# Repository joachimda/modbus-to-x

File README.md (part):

# Modbus-to-X

An ESP32-based hardware and firmware stack that bridges RS-485/Modbus field devices to modern network services such as MQTT, with a configuration-first UX for installers and maintainers.

## Table of Contents
- [Overview](#overview)
- [Architecture](#architecture)
  - [Hardware](#hardware)
  - [Firmware](#firmware)
- [Getting Started](#getting-started)
  - [Prerequisites](#prerequisites)
  - [Build and Flash](#build-and-flash)
  - [Release Automation](#release-automation)
  - [Local UI Development](#local-ui-development)
  - [HTTP API](#http-api)
- [Usage](#usage)
  - [First Boot and Network Setup](#first-boot-and-network-setup)
  - [Configuring Modbus Devices](#configuring-modbus-devices)
  - [MQTT Publishing](#mqtt-publishing)
  - [OTA Updates](#ota-updates)
- [Project Structure](#project-structure)
  - [Hardware Documentation](#hardware-documentation)
  - [Software Documentation](#software-documentation)
- [Acknowledgements](#acknowledgements)

## Overview
Modbus-to-X combines a custom ESP32 carrier board with firmware that polls Modbus RTU devices over RS-485, persists telemetry locally, and republishes structured payloads to MQTT brokers. 
The firmware exposes an onboard web interface for Wi-Fi provisioning, Modbus configuration, live device statistics, and log retrieval so field technicians can deploy the gateway without recompiling binaries.

## Architecture
The project is split between dedicated hardware design files and a PlatformIO firmware project. Hardware-specific documentation lives in [`hardware/`](hardware/); firmware, tooling, and UI assets live in [`software/`](software/).

### Hardware
- Four-layer ESP32 carrier featuring an ESP32-WROOM-32D module, MAX3485 RS-485 transceiver
- RJ12 Connector exposing differential RS-485 pair alongside field power for quick deployment.
- Wide input voltage range (4.5 - 30V)
- Supporting assets include datasheets, the hardware release policy, the compatibility table and a release record for each board revision under `hardware/`.

### Firmware
- PlatformIO-based ESP32 application primarily built with the Arduino framework.
- Library dependencies: ModbusMaster, PubSubClient, ArduinoJson, and ESPAsyncWebServer for protocol handling and a dynamic UI backend.
- A custom partition table separates user configurations from UI components, leaving user configurations untouched on filesystem uploads.
- Boot sequence mounts filesystem partitions, starts the async web server ("MBX Server"), initializes the Modbus scheduler, and spins up the MQTT manager.
- Configuration data for the Modbus bus, devices, and MQTT settings is stored in `/conf/*.json` on the dedicated config SPIFFS partition (`cfg`) and hot-reloaded without reflashing.
- MQTT passwords are stored in NVS preferences; `/conf/mqtt.json` contains non-sensitive fields.
- Default wiring, RS-485 guard times, Wi-Fi AP Portal credentials, and OTA parameters are centralized in [`Config.h`](software/modbus-to-mqtt/include/Config.h).
- Signed and manual HTTP updates use a bounded quiescence coordinator and a compiled recovery page; the lifecycle and protocol are documented in [`OTA_LIFECYCLE.md`](OTA_LIFECYCLE.md).

## Getting Started

### Prerequisites
- Modbus-to-X hardware (v0.2 alpha or later) and Modbus RTU devices wired to the RS-485 terminals.
- 4.5–40 VDC field power (buck input validated in the current design) and a USB-to-UART adapter if not using OTA uploads.
- Development host with Python 3, [PlatformIO Core](https://platformio.org/install/cli), and a working `git` toolchain. Required Python build dependencies are installed automatically by `scripts/install_build_deps.py` when PlatformIO runs.

### Build and Flash
1. Clone the repository and enter the firmware workspace:
   ```bash
   git clone https://github.com/joachimda/modbus-to-x.git
   cd modbus-to-x/software/modbus-to-mqtt
   ```
2. Choose an environment in `platformio.ini`:
   - `mbx-custom-board-dev` — development build, serial upload (default).
   - `mbx-custom-board-dev-ota` — development build, OTA upload (reads the device address from `MBX_DEV_OTA_HOST` and the OTA password from `MBX_DEV_OTA_PASSWORD`).
   - `mbx-custom-board-release` — release build (used by the GitHub Actions workflow).
   - `mbx-custom-board-release-primer` — primes a dev device to receive HTTP OTA updates (same environment variables as `mbx-custom-board-dev-ota`).
3. Build the firmware (PlatformIO will fetch dependencies and embed git metadata):
   ```bash
   pio run
   ```
4. Flash via USB/UART or OTA by selecting the matching environment:
   ```bash
   # Serial upload
   pio run -e mbx-custom-board-dev -t upload

   # OTA upload to a provisioned gateway; address and password come from your shell
   export MBX_DEV_OTA_HOST=<device-ip> MBX_DEV_OTA_PASSWORD=<ota-password>
   pio run -e mbx-custom-board-dev-ota -t upload
   ```
5. Upload the web UI and config assets to SPIFFS when they change:
   ```bash
   pio run -e mbx-custom-board-dev -t uploadfs
   ```

### Release Automation
Pushing a `v*` tag triggers the GitHub Actions workflow in `.github/workflows/main.yml` to build firmware + filesystem images and create a GitHub Release with the assets:
- `modbus-to-x.bin` (firmware)
- `modbus-to-x.fs.bin` (filesystem)
- `modbus-to-x.notes.txt` (release notes generated from the commit log since the previous tag)
- `modbus-to-x.manifest.json` (includes SHA-256 hashes and a signature generated from `OTA_SIGNING_KEY_PEM` and `KID`).

The same workflow can also be started manually (Actions → "Release OTA" → "Run workflow", or `gh workflow run "Release OTA" --ref main -f version=8.0.5-beta`). Enter the bare version without the `v` (`8.0.5` or `8.0.5-beta.1`); the workflow creates the tag `v<version>` on the selected ref (`gh` uses the repository's default branch when `--ref` is omitted), builds exactly as a tag push would, and pushes the tag together with the release. It refuses to run if that tag already exists or if the selected commit already carries a tag.

### Local UI Development
The `scripts/run_test_webserver.py` helper serves the `data/` directory with mocked API responses so you can iterate on the HTML/JS bundle without flashing the device:
```bash
cd software/modbus-to-mqtt
python3 scripts/run_test_webserver.py
# Visit http://127.0.0.1:8000
```
It injects correct MIME types, disables caching, and emulates the SPA's system, OTA, and administrative API behavior, including mutation-request protection.

Use `--provisioning-scenario delayed`, `temporary`, `completion-unavailable`, `readiness-html`, or another listed scenario to exercise captive handoff failures. Running the mock on port 80 allows its loopback station address to complete the full dashboard handoff.

Use `--ota-scenario success`, `failure`, or `sse-loss` to exercise OTA
admission, lifecycle progress, status-poll fallback, recovery, and reboot UI.

### HTTP API

See the [HTTP API request contract](HTTP_API.md) for the route and method matrix, browser cross-site protections, OTA authorization behavior, and non-browser client examples.

## Usage

### First Boot and Network Setup
1. Power the gateway; it will advertise a Wi-Fi AP using the defaults defined in `Config.h` (`MODBUS-MQTT-BRIDGE` / `you-shall-not-pass`).
2. Connect to the AP. The ESP will try getting 192.168.4.1 from DHCP. If supported on your OS, you will be prompted to open the Captive Portal and redirected automatically. If these fail, check your router for the device's IP address, and use your browser to open the configuration page `http://192.168.4.1/`. 
3. Follow the on-screen guidance to scan, join, or provision hidden networks, optionally specifying static IP parameters before saving.
4. After a saved network connection succeeds, the portal requests an acknowledged reboot, waits for the device to return in station mode, and opens the dashboard at the reported address. Temporary connections remain in the portal until a saved attempt succeeds.

### Configuring Modbus Devices
- Use **Configure Modbus** to edit the RS-485 bus, add devices, and define datapoints. Modbus configurations are stored in the config partition at `/conf/config.json` and can be applied live without rebooting.
- Configuration files follow the schema in `software/modbus-to-mqtt/data/conf/schema.json`; the excerpt below shows the datapoint fields. Each datapoint specifies the function code, register address, data type, scale, and engineering units that will be published when polled. Registers are decoded by `dataType` before the scale is applied: `int16`/`uint16` use one register (optionally a byte via `registerSlice`), `int32`/`uint32`/`float32` use two and `int64`/`uint64` four registers, in the `wordOrder` `big` (default, first register = most significant word) or `little`. `numOfRegisters` below the type's width is raised to it when the configuration loads. FC6 writes one register, so saving FC6 with a 32-bit or 64-bit type is rejected; a stored configuration that already combines them loads as `uint16` (the encoding every FC6 value had before data types were honoured, so nothing changes for it) with a logged warning.
- `bus.baud` must be an integer of at least 1200, the lowest rate the bus form offers; a configuration below it, or with a non-integer value, is rejected with `invalid_baud_rate`. A stored configuration that fails this check is logged at boot and leaves Modbus disabled until it is corrected in **Configure Modbus**.
- A datapoint's `poll_interval` (seconds) must be a whole number from 0 to 2147483, and `poll_interval_ms` from 0 to 2147483647 (about 24.8 days); `poll_interval_ms` wins when both are present. A save with anything else is rejected with `invalid_poll_interval`. A configuration already stored on the device keeps loading: at boot an out-of-range interval is brought into range (negative becomes 0, a fraction is rounded down, a larger number becomes the maximum) and logged as `poll_interval_repaired`. Enabling Modbus again at runtime polls every datapoint once and restarts its interval. The limit keeps polling deadlines unambiguous when the 32-bit millisecond uptime counter wraps after about 49.7 days.
- Per-device MQTT publishing and Home Assistant discovery can be toggled in the Modbus config; discovery publishes retained entity definitions for read/write datapoints.
  Example (excerpt):
  ```json
  {
    "devices": [
      {
        "name": "Boiler",
        "slaveId": 10,
        "mqttEnabled": true,
        "homeassistantDiscoveryEnabled": true,
        "dataPoints": [
          {
            "id": "temp",
            "name": "Temperature",
            "function": 4,
            "address": 100,
            "numOfRegisters": 1,
            "dataType": "int16",
            "scale": 0.1,
            "unit": "C",
            "topic": "plant/boiler/temp_c"
          },
          {
            "id": "flow",
            "name": "Flow",
            "function": 3,
            "address": 200,
            "numOfRegisters": 2,
            "dataType": "float32",
            "wordOrder": "little",
            "scale": 1,
            "unit": "m3/h"
          }
        ]
      }
    ]
  }
  ```

#### Wavin AHC 9000
The Wavin AHC 9000 floor-heating controller (also sold as Jablotron AC-116) uses Modbus RTU framing but answers only its own function codes, so standard reads return `IllegalFunction`. Use function `67` (0x43, read) and `68` (0x44, write). These address a register by `category`, `page` and a register index, which goes in `address`, each 0-255. Reads cover up to 22 registers; writes set one 16-bit register and follow the FC6 rules.

- Bus: 38400 baud, `8N1`. The controller always answers slave address 1.
- Commonly used registers, from Wavin's Modbus description for the AHC 9000 (14-08-2013, [copy in jascdk/wavin_ahc9000_advanced_mqtt](https://github.com/jascdk/wavin_ahc9000_advanced_mqtt/tree/main/Modbus%20Documentation)) and the community projects ([niklascp/Wavin-AHC-9000-mqtt](https://github.com/niklascp/Wavin-AHC-9000-mqtt), [spiff42/wavin-python](https://github.com/spiff42/wavin-python)), checked on an AHC 9000 with wireless thermostats. Thermostats (elements) and channels are numbered from 0; a channel's page is its output number minus one.

  | Category | Page | Index | Value |
  | --- | --- | --- | --- |
  | 1 (elements) | element/thermostat number | 2 | Channel assignment, bitmask of the channels this thermostat drives |
  | 1 (elements) | element/thermostat number | 4 | Air temperature, `int16` × 0.1 °C |
  | 1 (elements) | element/thermostat number | 8 | Status; bit `0x8000` alive, `0x0800` lost, `0x0200` low battery, `0x0010` is a thermostat |
  | 1 (elements) | element/thermostat number | 9 | RSSI: high byte at the thermostat, low byte at the controller; signed, 0 = -74 dBm, 0.5 dB per step |
  | 1 (elements) | element/thermostat number | 10 | Battery in 10 % steps (9 = 90 %); 0 until the thermostat has reported |
  | 1 (elements) | element/thermostat number | 11 | Primary channel (sync group) |
  | 2 (packed data) | channel number | 0 | Manual setpoint, `int16` × 0.1 °C (writable) |
  | 2 (packed data) | channel number | 1, 2 | Comfort and eco setpoints, `int16` × 0.1 °C |
  | 2 (packed data) | channel number | 4 | Standby setpoint, `int16` × 0.1 °C (writable) |
  | 2 (packed data) | channel number | 7 | Configuration; low 3 bits are the mode (0 manual, 1 permanent standby, 2 eco, 3 comfort, 4 party, 5 holiday) and bit `0x0008` enables the week schedule |
  | 2 (packed data) | channel number | 8, 9 | Minimum and maximum setpoint the user can set on the thermostat, `int16` × 0.1 °C. The controller does not clamp 0x44 writes to this range |
  | 2 (packed data) | channel number | 16 | Desired temperature the channel currently heats to, `int16` × 0.1 °C (read only) |
  | 3 (channels) | channel number | 0 | Timer event; bit `0x0010` is set while the output is on, the low 4 bits are the current timer event (1 idle, 7 output on) |
  | 3 (channels) | channel number | 1 | Actuator current in 0.54 mA units |
  | 3 (channels) | channel number | 2 | Primary element **plus one** in the low 6 bits (`0x00C1` = element 0, 0 = no thermostat); `0x0400` means all thermostats lost; `0x0080`/`0x0040` store the party/holiday preference and `0x4000` means the channel syncs its parameters in the next frame |

  ```json
  {
    "version": 1,
    "bus": { "enabled": true, "baud": 38400, "serialFormat": "8N1" },
    "devices": [
      {
        "name": "Wavin",
        "slaveId": 1,
        "mqttEnabled": true,
        "homeassistantDiscoveryEnabled": true,
        "dataPoints": [
          { "id": "zone1_temp", "name": "Zone 1 temperature", "function": 67,
            "category": 1, "page": 0, "address": 4, "numOfRegisters": 1,
            "dataType": "int16", "scale": 0.1, "unit": "C", "poll_interval": 30 },
          { "id": "zone1_setpoint", "name": "Zone 1 setpoint", "function": 67,
            "category": 2, "page": 0, "address": 0, "numOfRegisters": 1,
            "dataType": "int16", "scale": 0.1, "unit": "C", "poll_interval": 30 },
          { "id": "zone1_setpoint_set", "name": "Zone 1 setpoint", "function": 68,
            "category": 2, "page": 0, "address": 0, "numOfRegisters": 1,
            "dataType": "int16", "scale": 0.1 }
        ]
      }
    ]
  }
  ```
- The clock (category 5, page 0: year, month, day, weekday with 0 = Monday, hour, minute, second) must be read or written as one 7-register page; single-register writes are not answered.
- A wall display (DS-9000) may share the bus as a second master. Bytes that cannot be the reply to the outstanding request (another slave or function, more registers than requested, the display's own requests, or a bad CRC) are skipped while waiting. An attempt waits 500 ms for the reply to start (`WAVIN_TURNAROUND_MS`) plus the time the reply takes at the bus's baud rate (about 13 ms for 22 registers at 38400 8N1, 409 ms at 1200). A read or 0x44 write that times out or fails its CRC is retried after a random 100–250 ms pause, up to 3 attempts in total (`WAVIN_READ_ATTEMPTS`, `WAVIN_WRITE_ATTEMPTS`), but a retry only starts if it still fits the 2000 ms budget for the attempts and their pauses (`WAVIN_TRANSACTION_BUDGET_MS`, derived from the OTA quiescence bound): at 38400 all three attempts normally fit, at 9600 a 22-register read usually gets two, at 1200 one. After a final failure, input is discarded until the line has been quiet for 50 ms (`WAVIN_SETTLE_QUIET_MS`), for at most 150 ms (`WAVIN_SETTLE_MAX_MS`) beyond the budget, so a reply that arrives late is not taken for the reply to the next request. A 0x44 write sets absolute values, so repeating it after a lost reply cannot double-apply; if the same register is changed at the wall display in the 0.6–0.8 s (at 38400) between a lost reply and the retry, the retry overwrites that change (last writer wins, as it does without retries when the display edit follows the write). A reply carrying fewer registers than requested is accepted; only the registers received are decoded.

### MQTT Publishing
- Configure broker host, port, credentials, and optional root topic via the **Configure MQTT** page or by editing `/conf/mqtt.json`. The firmware automatically extracts hostnames from URLs and persists the MQTT password in NVS preferences.
- When Modbus reads succeed, datapoint values are published to MQTT using either the exact per-datapoint topic override or the default pattern `<root>/<device>/<datapoint>` with slugified device and datapoint names.
- Published values are decoded by the datapoint's `dataType` (and `wordOrder` for multi-register types) before the scale is applied, then printed with as many decimals as the scale has (`0.01` → `-2.00`, `1` → `1234`, `0.5` → `12.5`); `float32` values print the shortest decimal (7 to 9 significant digits) that reads back as the same value; `int64`/`uint64` values keep every digit at integral scales and round through double precision at fractional ones. Coils and discrete inputs publish `1`/`0`; `TEXT` datapoints publish the ASCII content of their registers. A read that returns fewer registers than the data type needs is logged and not published.
- A writable datapoint treats its configured `topic` as a base and subscribes only to `<base>/set`; an empty base uses the same default resolution as a readable datapoint before `/set` is appended. Commands must be published without MQTT retain. There is deliberately no subscription on the legacy base/state topic.
- Existing state consumers require no changes. Existing command publishers and automations must migrate from `<base>` to `<base>/set`; retained state left on `<base>` is safe because the gateway no longer subscribes there.
- Home Assistant sensors advertise the resolved state topic. Switches and numbers advertise the derived `/set` command topic and use a readable datapoint with the same resolved base as state feedback, or remain optimistic when no matching read exists. Number entities advertise the data type's range times the scale as `min`/`max` and the absolute scale as `step` (never below Home Assistant's minimum of `0.001`).
- FC5 coil commands accept only `0`, `1`, `false`, or `true` after surrounding whitespace is removed; the words are case-insensitive.
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
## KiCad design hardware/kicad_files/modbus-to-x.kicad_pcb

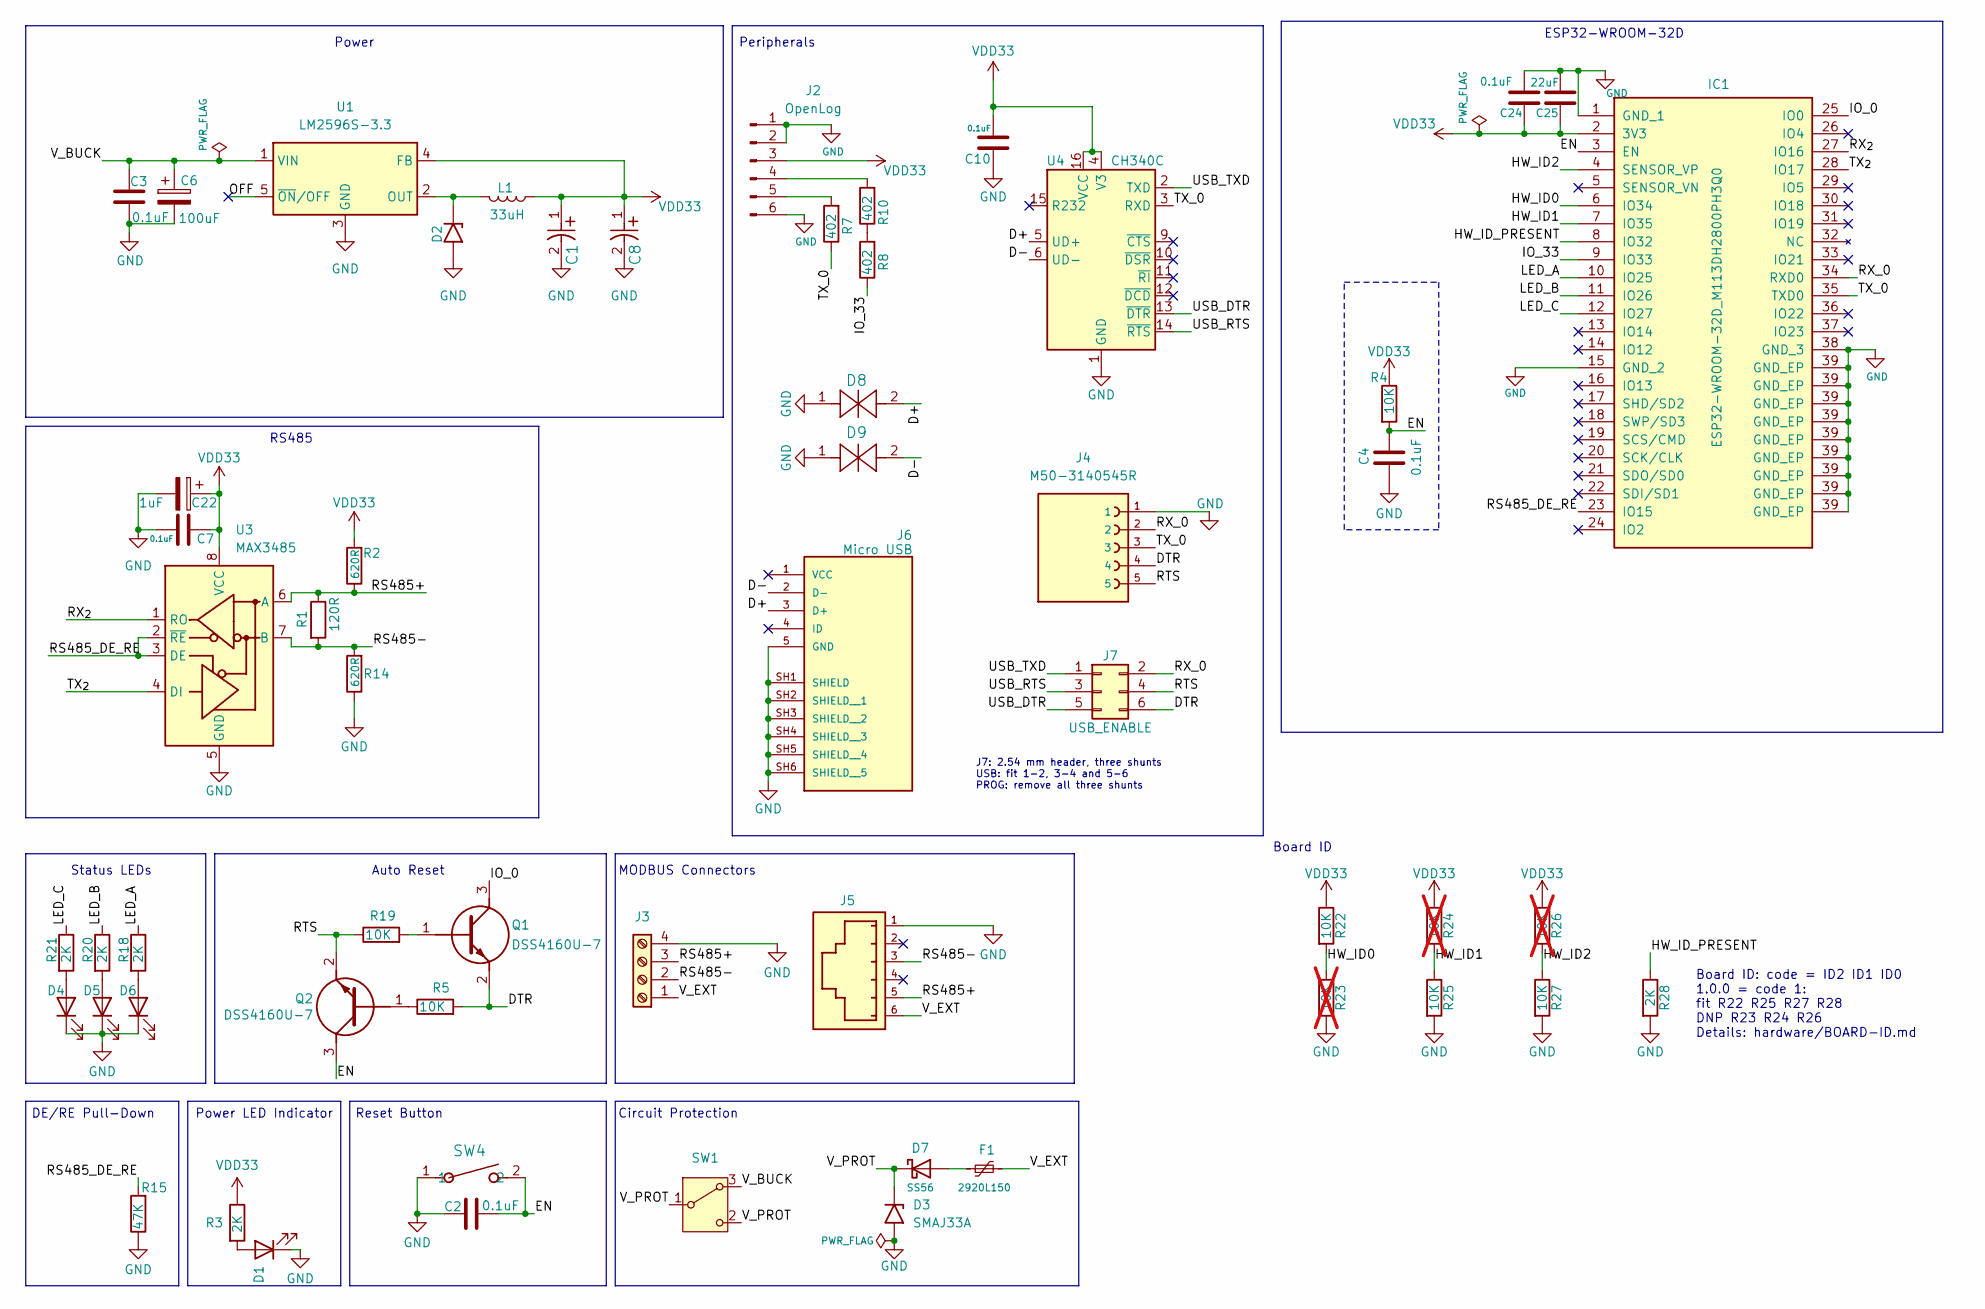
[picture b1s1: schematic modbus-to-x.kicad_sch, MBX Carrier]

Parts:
C1, C8: 330uF; T495D337K006ATE100; MPN T495D337K006ATE100
C2, C4, C7, C10, C24: 0.1uF; C_0805_2012Metric; Voltage 50V; MPN GCD21BR71H104KA01L
C3: 0.1uF; C_0603_1608Metric; Voltage 50V; MPN C0603C104K5RACTU
C6: 100uF; ESY107M050AG3AA; Voltage 50V; MPN ESY107M050AG3AA
C22: 1uF; CP_Elec_4x5.4; Voltage 50V; MPN NACE1R0M50V4X5.5TR15F
C25: 22uF; C_0805_2012Metric_Pad1.18x1.45mm_HandSolder; Voltage 16V; MPN CL21A226MOCLRNC
D1, D4, D5, D6: LED; LED_0402_1005Metric_Pad0.77x0.64mm_HandSolder; MPN LW QH8G-Q2OO-3K5L-1
D2: B340LA-13-F; D_SMA_Handsoldering; MPN B340LA-13-F
D3: SMAJ33A; D_SMA; MPN SMAJ33A
D7: SS56; D_SMA; MPN SS56
D8, D9: PESD0402-140; PESD0402-140_LTF; MPN PESD0402-140
F1: 2920L150; Fuse_2920_7451Metric; MPN 2920L150/60MR
IC1: ESP32-WROOM-32D_M113DH2800PH3Q0; ESP32-WROOM-32D_ANT_SILK_REMOVED; MPN M113DH2800PH3Q0
J2: OpenLog; MBX_PinHeader_1x06_P2.54mm_Vertical; MPN Pin Header 2.54mm (Mixed lengths)
J3: Screw_Terminal_01x04; TerminalBlock_Phoenix_MKDS-1,5-4-5.08_1x04_P5.08mm_Horizont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
J4: M50-3140545R; HARWIN_M50-3140545R; MPN M50-3140545R
J5: 615006138421; RJ12_615006138421; MPN 615006138421
J6: Micro USB; AMPHENOL_10118194-0001LF; MPN 10118194-0001LF
J7: USB_ENABLE; PinHeader_2x03_P2.54mm_Vertical; MPN Pin Header 2.54mm (Mixed lengths)
L1: 33uH; IND_BOURNS_SRR1260; MPN SRR1260-330M
Q1, Q2: DSS4160U-7; SOT65P210X110-3N; MPN DSS4160U-7
R1: 120R; R_1206_3216Metric_Pad1.30x1.75mm_HandSolder; MPN RC1206FR-13120RL
R2, R14: 620R; R_0805_2012Metric_Pad1.20x1.40mm_HandSolder; MPN 1550805S8F6200T5E
R3, R18, R20, R21, R28: 2K; R_0603_1608Metric_Pad0.98x0.95mm_HandSolder; MPN 155TC0325B2001T5H
R4, R5, R19, R22, R25, R27: 10K; R_0603_1608Metric; MPN RT0603DRE0710KL
R7, R8, R10: 402; MBX_R_0402_1005Metric; MPN RC0402FR-07402RL
R15: 47K; R_0805_2012Metric_Pad1.20x1.40mm_HandSolder; MPN 1550805S8F4702T5E
R23, R24, R26: 10K; R_0603_1608Metric; MPN RT0603DRE0710KL; not fitted
SW1: SS12D00G3; SW_Slide-03_Wuerth-WS-SLTV_10x2.5x6.4_P2.54mm; MPN SS12D00G3
SW4: 3983; SW_3983_ADA; MPN Adafruit-3983
U1: LM2596S-3.3; TO-263-5_TabPin3_silk_fix; MPN LM2596S-3.3-EV
U3: MAX3485; SOIC-8_3.9x4.9mm_P1.27mm; MPN MAX3485CSA+T
U4: CH340C; SOIC-16_3.9x9.9mm_P1.27mm; MPN CH340C

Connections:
/D+: D8.2, J6.3 (D+), U4.5 (UD+)
/D-: D9.2, J6.2 (D-), U4.6 (UD-)
/DTR: J4.4, J7.6, Q1.2 (E), R5.2
/EN: C2.1, C4.1, IC1.3 (EN), Q2.3 (C), R4.2, SW4.2
/HW_ID0: IC1.6 (IO34), R22.2, R23.1
/HW_ID1: IC1.7 (IO35), R24.2, R25.1
/HW_ID2: IC1.4 (SENSOR_VP), R26.2, R27.1
/HW_ID_PRESENT: IC1.8 (IO32), R28.1
/IO_0: IC1.25 (IO0), Q1.3 (C)
/IO_33: IC1.9 (IO33), R8.1
/LED_A: IC1.10 (IO25), R18.1
/LED_B: IC1.11 (IO26), R20.1
/LED_C: IC1.12 (IO27), R21.1
/OFF: U1.5 (~ON/OFF)
/RS485+: J3.3, J5.5, R1.1, R2.1, U3.6 (A)
/RS485-: J3.2, J5.3, R1.2, R14.2, U3.7 (B)
/RS485_DE_RE: IC1.23 (IO15), R15.2, U3.2 (~RE), U3.3 (DE)
/RTS: J4.5, J7.4, Q2.2 (E), R19.1
/RX_0: IC1.34 (RXD0), J4.2, J7.2
/RX_{2}: IC1.27 (IO16), U3.1 (RO)
/TX_0: IC1.35 (TXD0), J4.3, R7.1, U4.3 (RXD)
/TX_{2}: IC1.28 (IO17), U3.4 (DI)
/USB_DTR: J7.5, U4.13 (~DTR)
/USB_RTS: J7.3, U4.14 (~RTS)
/USB_TXD: J7.1, U4.2 (TXD)
/V_BUCK: C3.1, C6.1, SW1.3 (A), U1.1 (VIN)
/V_EXT: F1.2, J3.1, J5.6
/V_PROT: D3.1 (A1), D7.1 (K), SW1.1 (B), SW1.2 (C)
GND: C1.2, C2.2, C3.2, C4.2, C6.2, C7.2, C8.2, C10.1, C22.2, C24.1, C25.1, D1.1 (K), D2.2 (A2), D3.2 (A2), D4.1 (K), D5.1 (K), D6.1 (K), D8.1, D9.1, IC1.1 (GND_1), IC1.15 (GND_2), IC1.38 (GND_3), IC1.39 (GND_EP), J2.1, J2.2, J2.6, J3.4, J4.1, J5.1, J6.5 (GND), J6.SH1 (SHIELD), J6.SH2 (SHIELD__1), J6.SH3 (SHIELD__2), J6.SH4 (SHIELD__3), J6.SH5 (SHIELD__4), J6.SH6 (SHIELD__5), R14.1, R15.1, R23.2, R25.2, R27.2, R28.2, SW4.1, U1.3 (GND), U3.5 (GND), U4.1 (GND)
unnamed: D1.2 (A), R3.2
unnamed: D2.1 (A1), L1.2, U1.2 (OUT)
unnamed: D4.2 (A), R21.2
unnamed: D5.2 (A), R20.2
unnamed: D6.2 (A), R18.2
unnamed: D7.2 (A), F1.1
unnamed: J2.4, R10.2
unnamed: J2.5, R7.2
unnamed: Q1.1 (B), R19.2
unnamed: Q2.1 (B), R5.1
unnamed: R8.2, R10.1
VDD33: C1.1, C7.1, C8.1, C10.2, C22.1, C24.2, C25.2, IC1.2 (3V3), J2.3, L1.1, R2.2, R3.1, R4.1, R22.1, R24.1, R26.1, U1.4 (FB), U3.8 (VCC), U4.4 (V3), U4.16 (VCC)

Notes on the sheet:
J7: 2.54 mm header, three shunts USB: fit 1-2, 3-4 and 5-6 PROG: remove all three shunts
MODBUS Connectors
Power LED Indicator
Auto Reset
ESP32-WROOM-32D
Peripherals
Circuit Protection
Board ID: code = ID2 ID1 ID0 1.0.0 = code 1: fit R22 R25 R27 R28 DNP R23 R24 R26 Details: hardware/BOARD-ID.md
Power
Status LEDs
Reset Button
RS485
Board ID
DE/RE Pull-Down

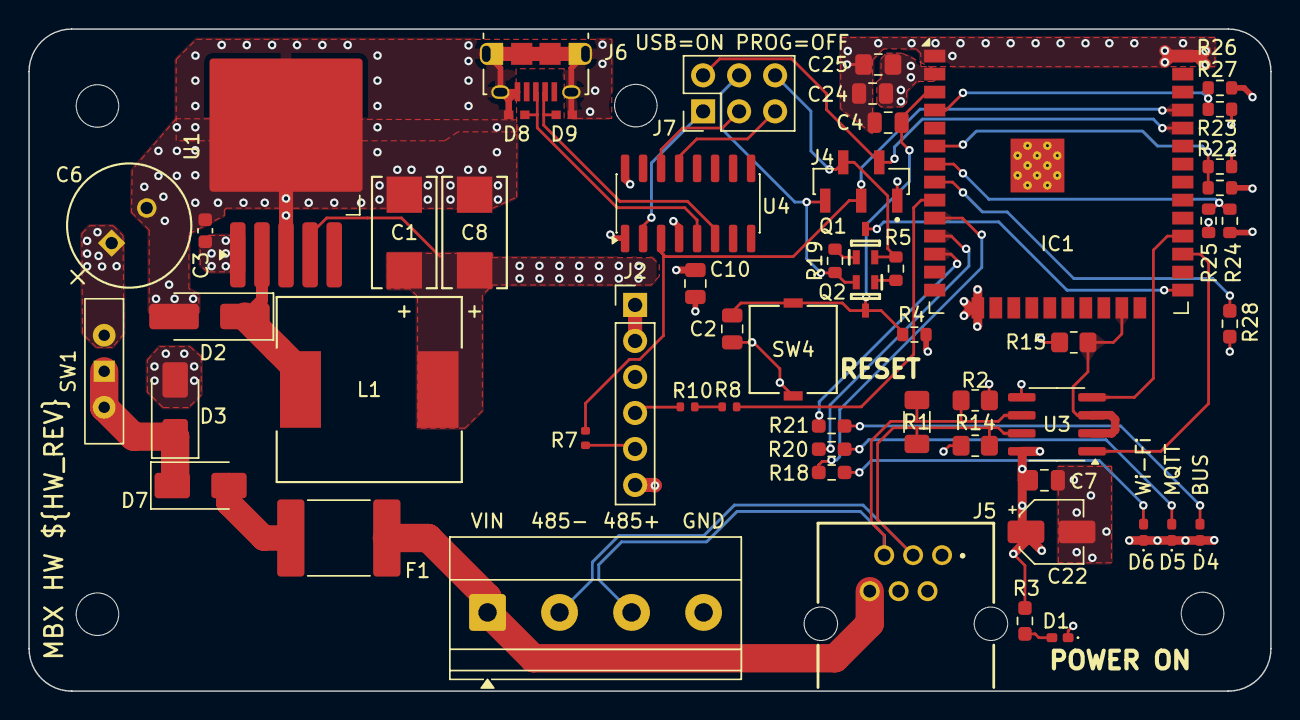
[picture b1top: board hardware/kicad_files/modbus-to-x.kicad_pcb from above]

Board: 4 copper layers, 87.6 x 46.7 mm, 57 parts (0 on the bottom side), 40 nets.

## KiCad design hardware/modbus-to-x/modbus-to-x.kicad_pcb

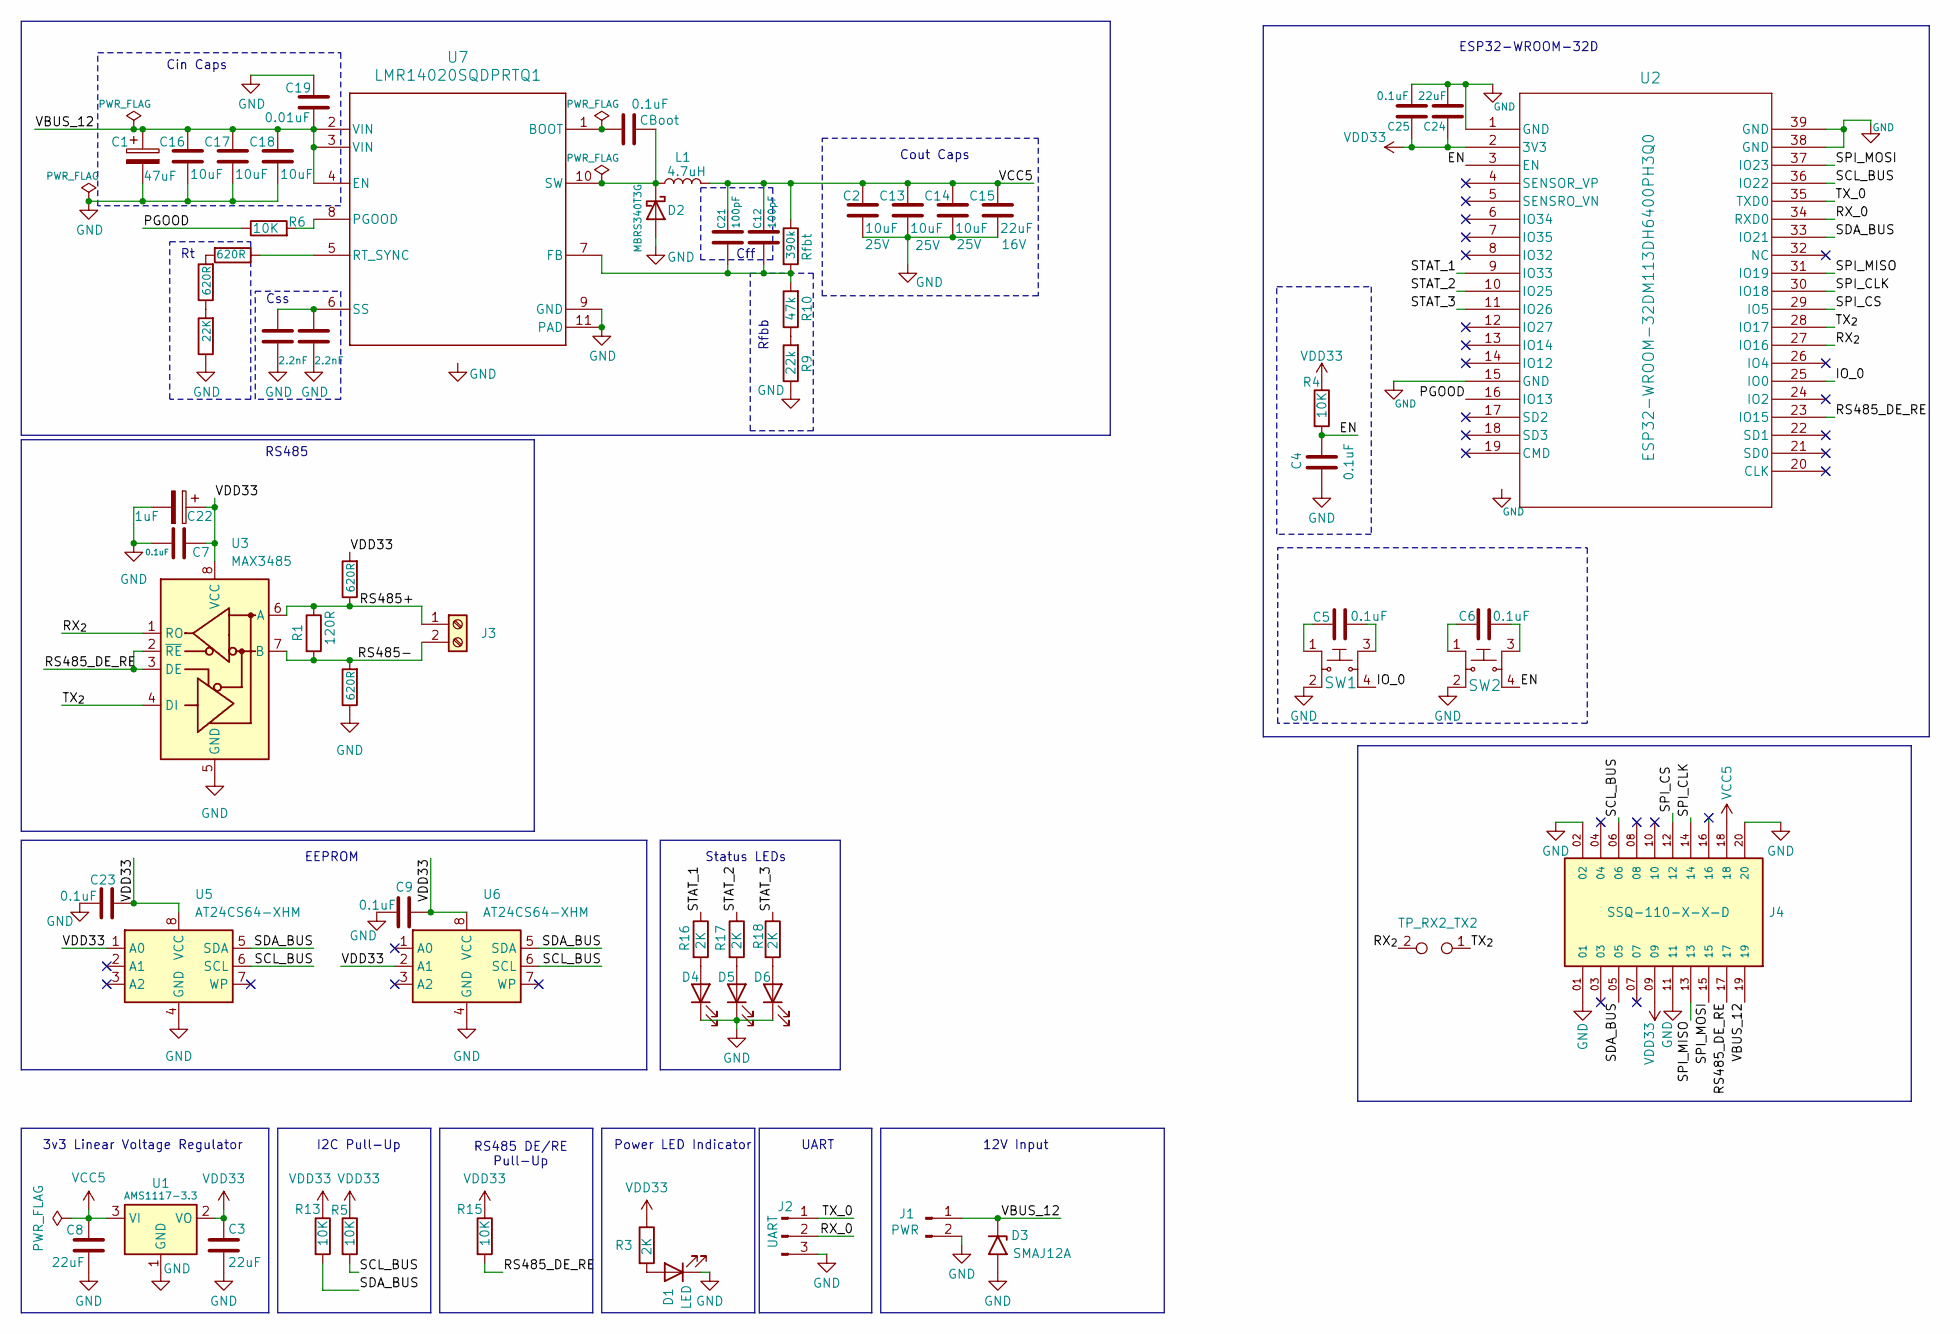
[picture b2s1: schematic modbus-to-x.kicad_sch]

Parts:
C1: 47uF; CP_Elec_6.3x5.4; Voltage 35V; PartNo CSMK047/35
C2, C13, C14, C16, C17, C18: 10uF; C_0805_2012Metric_Pad1.18x1.45mm_HandSolder; Voltage 25V; PartNo CL21A106KAYNNNF
C3, C8, C15, C24: 22uF; C_0805_2012Metric_Pad1.18x1.45mm_HandSolder; Voltage 16V; PartNo CL21A226MOCLRNC
C4, C5, C6, C7, C9, C23, C25: 0.1uF; C_1206_3216Metric_Pad1.33x1.80mm_HandSolder; Voltage 50V; PartNo CVNF100K12X
C10: 0.1uF; C_0402_1005Metric_Pad0.74x0.62mm_HandSolder; Voltage 16V; PartNo CC0402MRX5R7BB104
C11, C20: 2.2nF; C_0805_2012Metric_Pad1.18x1.45mm_HandSolder; Voltage 50V; PartNo RND 1500805B222J500NT
C12, C21: 100pF; C_0805_2012Metric_Pad1.18x1.45mm_HandSolder; Voltage 50V; PartNo RND 1500805N101J500NT
C19: 0.01uF; C_0402_1005Metric_Pad0.74x0.62mm_HandSolder; Voltage 50V; PartNo GCM155R71H103KA55D
C22: 1uF; CP_Elec_4x5.4; Voltage 50V; PartNo CHS0001/50
D1, D4, D5, D6: LED; LED_0402_1005Metric_Pad0.77x0.64mm_HandSolder; PartNo LW QH8G-Q2OO-3K5L-1
D2: MBRS340T3G; D_SMB-SMC_Universal_Handsoldering; PartNo MBRS340T3G
D3: SMAJ12A; D_SMA_Handsoldering; PartNo SMAJ12A
J1: PWR; Screw_Terminal_3.5mm-2
J2: UART; Screw_Terminal_3.5mm-3
J3: Screw_Terminal_3.5mm_2; Screw_Terminal_3.5mm-2
J4: SSQ-110-X-X-D; SAMTEC_SSQ-110-X-X-D; PARTREV A
L1: 4.7uH; L_Wurth_WE-LQS-4012; PartNo WE 74404041047
R1: 120R; R_1206_3216Metric_Pad1.30x1.75mm_HandSolder; PartNo RND 1551206S4F1000T5E
R2, R7, R12, R14: 620R; R_0805_2012Metric_Pad1.20x1.40mm_HandSolder; PartNo RND 1550805S8F6200T5E
R3, R16, R17, R18: 2K; R_0603_1608Metric_Pad0.98x0.95mm_HandSolder; PartNo RND 155TC0325B2001T5H
R4, R5, R6, R13, R15: 10K; R_0805_2012Metric_Pad1.20x1.40mm_HandSolder; PartNo RND 155TC0525B1002T5J
R8: 390k; R_0402_1005Metric_Pad0.72x0.64mm_HandSolder; PartNo RC0402FR-07390KL
R9: 22k; R_0603_1608Metric_Pad0.98x0.95mm_HandSolder; PartNo RND 155TC0325B2202T5H
R10: 47k; R_0805_2012Metric_Pad1.20x1.40mm_HandSolder; PartNo RND 1550805S8F4702T5E
R11: 22K; R_0603_1608Metric_Pad0.98x0.95mm_HandSolder; PartNo RND 155TC0325B2202T5H
SW1, SW2: 1825910-7; Switch_Tactile_SMD_6x6mm_PTS645; MPN 1825910-7; Digi-Key_PN 450-1804-ND
TP_RX2_TX2: TestPoint_2Pole; PinHeader_1x02_P2.54mm_Vertical
U1: AMS1117-3.3; SOT-223-3_TabPin2; PartNo AMS1117-3.3
U2: ESP32-WROOM-32DM113DH6400PH3Q0; ESP32-WROOM-32DM113DH6400PH3Q0_EXP
U3: MAX3485; SOIC-8_3.9x4.9mm_P1.27mm; PartNo MAX485
U5, U6: AT24CS64-XHM; TSSOP-8_4.4x3mm_P0.65mm; PartNo AT24CS64
U7: LMR14020SQDPRTQ1; DPR0010A_3mm_thermals; PartNo LMR14020Q

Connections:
/EN: C4.1, J4.08, R4.2, SW2.4, U2.3 (EN)
/GPIO12: J4.03, U2.14 (IO12)
/GPIO14: J4.04, U2.13 (IO14)
/GPIO27: J4.07, U2.12 (IO27)
/GPIO_34: J4.10, U2.6 (IO34)
/GPIO_35: J4.16, U2.7 (IO35)
/IO_0: SW1.4, U2.25 (IO0)
/PGOOD: R6.1, U2.16 (IO13)
/RS485+: J3.1, R1.1, R2.1, U3.6 (A)
/RS485-: J3.2, R1.2, R14.2, U3.7 (B)
/RS485_DE_RE: J4.17, R15.2, U2.23 (IO15), U3.2 (~RE), U3.3 (DE)
/RX_0: J2.2, U2.34 (RXD0)
/RX_{2}: TP_RX2_TX2.2, U2.27 (IO16), U3.1 (RO)
/SCL_BUS: J4.06, R5.2, U2.36 (IO22), U5.6 (SCL), U6.6 (SCL)
/SDA_BUS: J4.05, R13.2, U2.33 (IO21), U5.5 (SDA), U6.5 (SDA)
/SPI_CLK: J4.14, U2.30 (IO18)
/SPI_CS: J4.12, U2.29 (IO5)
/SPI_MISO: J4.13, U2.31 (IO19)
/SPI_MOSI: J4.15, U2.37 (IO23)
/STAT_1: R16.1, U2.9 (IO33)
/STAT_2: R17.1, U2.10 (IO25)
/STAT_3: R18.1, U2.11 (IO26)
/TX_0: J2.1, U2.35 (TXD0)
/TX_{2}: TP_RX2_TX2.1, U2.28 (IO17), U3.4 (DI)
/VBUS_12: C1.1, C16.2, C17.2, C18.2, C19.1, D3.1 (A1), J1.1, J4.19, U7.2 (VIN), U7.3 (VIN), U7.4 (EN)
GND: C1.2, C2.1, C3.2, C4.2, C7.2, C8.2, C9.2, C11.1, C13.1, C14.1, C15.1, C16.1, C17.1, C18.1, C19.2, C20.1, C22.2, C23.1, C24.1, C25.1, D1.1 (K), D2.2 (A), D3.2 (A2), D4.1 (K), D5.1 (K), D6.1 (K), J1.2, J2.3, J4.01, J4.02, J4.11, J4.20, R9.1, R11.1, R14.1, SW1.2, SW2.2, U1.1 (GND), U2.1 (GND), U2.15 (GND), U2.38 (GND), U2.39 (GND_STITCH), U2.V (GND_STITCH), U3.5 (GND), U5.4 (GND), U6.4 (GND), U7.9 (GND), U7.11 (PAD), U7.V (GND_STITCH)
unnamed: C5.1, SW1.3
unnamed: C5.2, SW1.1
unnamed: C6.1, SW2.3
unnamed: C6.2, SW2.1
unnamed: D1.2 (A), R3.2
unnamed: C10.1, D2.1 (K), L1.1, U7.10 (SW)
unnamed: D4.2 (A), R16.2
unnamed: D5.2 (A), R17.2
unnamed: D6.2 (A), R18.2
unnamed: R9.2, R10.1
unnamed: R7.1, R11.2
unnamed: R7.2, R12.2
unnamed: C10.2, U7.1 (BOOT)
unnamed: C12.1, C21.1, R8.2, R10.2, U7.7 (FB)
unnamed: R6.2, U7.8 (PGOOD)
unnamed: R12.1, U7.5 (RT_SYNC)
unnamed: C11.2, C20.2, U7.6 (SS)
VCC5: C2.2, C8.1, C12.2, C13.2, C14.2, C15.2, C21.2, J4.18, L1.2, R8.1, U1.3 (VI)
VDD33: C3.1, C7.1, C9.1, C22.1, C23.2, C24.2, C25.2, J4.09, R2.2, R3.1, R4.1, R5.1, R13.1, R15.1, U1.2 (VO), U2.2 (3V3), U3.8 (VCC), U5.1 (A0), U5.8 (VCC), U6.2 (A1), U6.8 (VCC)

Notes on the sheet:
Cout Caps
12V Input
EEPROM
Power LED Indicator
ESP32-WROOM-32D
Cff
I2C Pull-Up
Rfbb
Cin Caps
3v3 Linear Voltage Regulator
UART
Css
Status LEDs
RS485
RS485 DE/RE Pull-Up

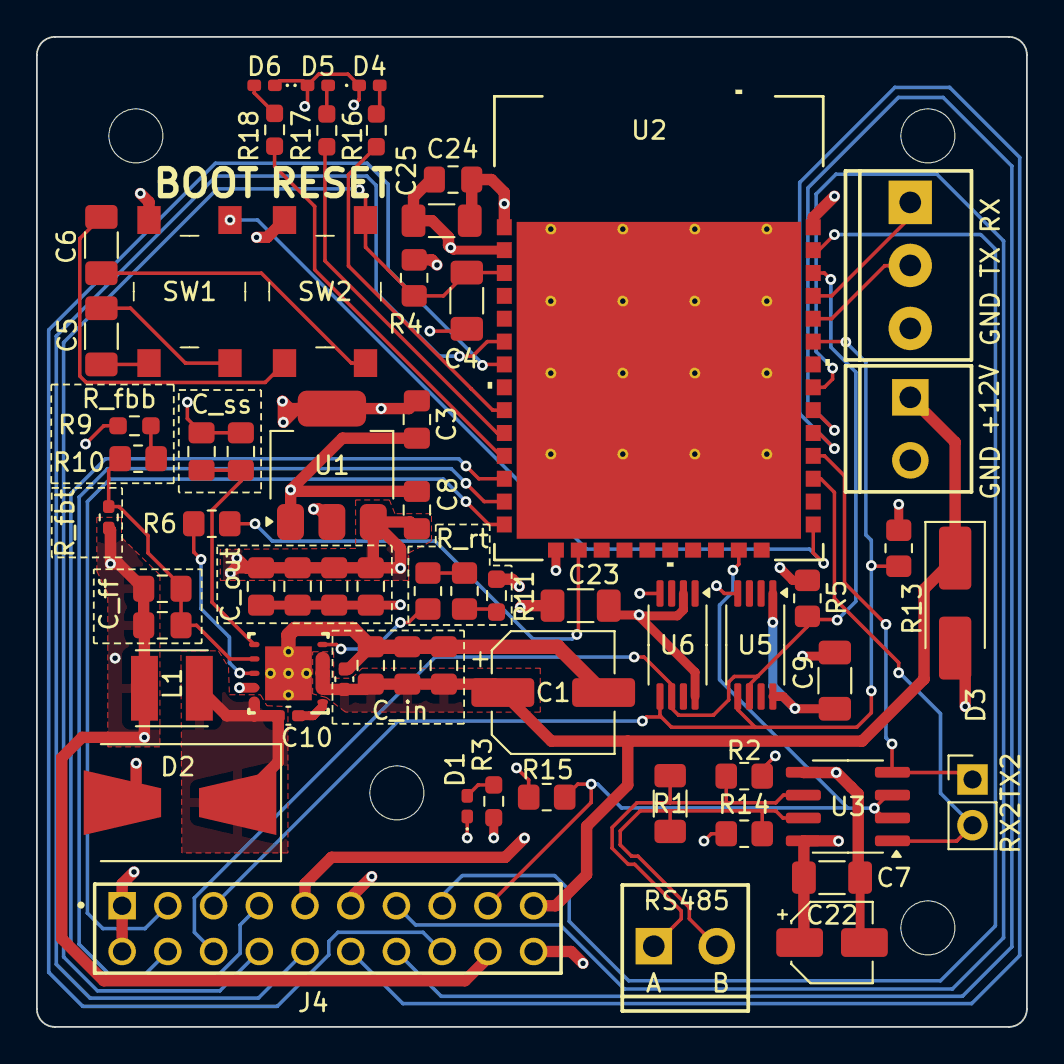
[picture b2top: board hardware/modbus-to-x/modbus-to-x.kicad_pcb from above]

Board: 4 copper layers, 55.0 x 55.0 mm, 63 parts (0 on the bottom side), 45 nets.

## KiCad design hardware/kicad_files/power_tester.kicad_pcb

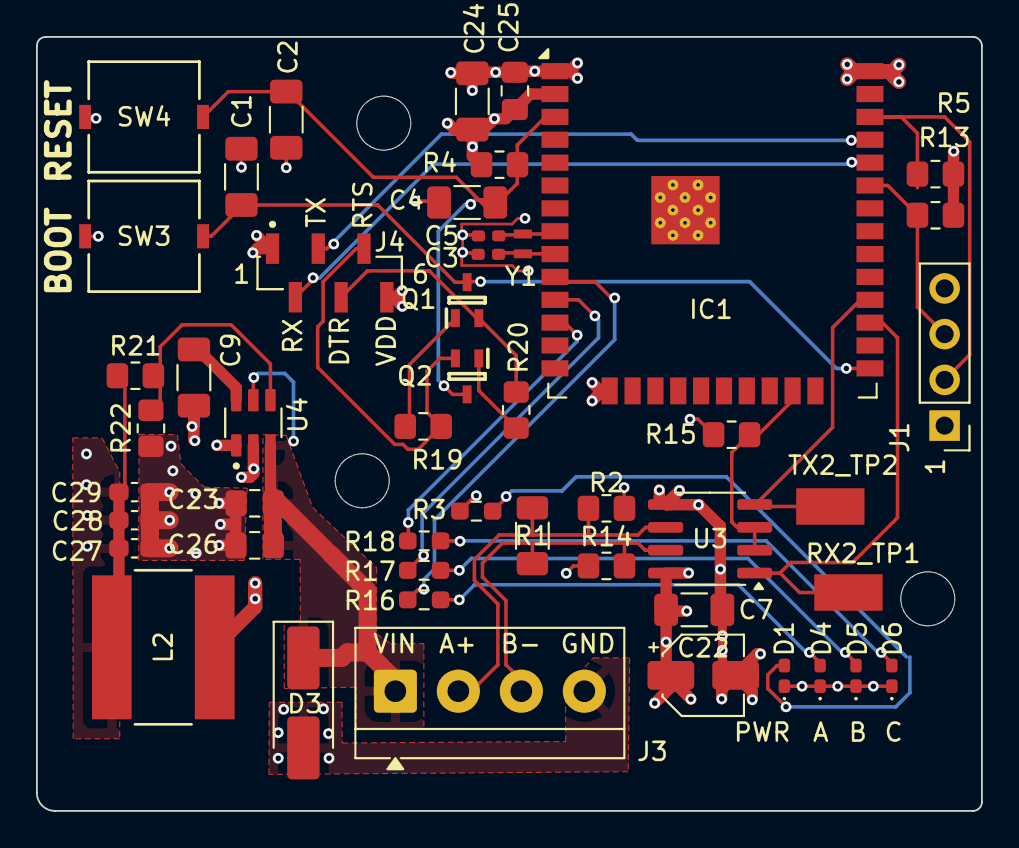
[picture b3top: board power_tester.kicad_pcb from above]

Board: 4 copper layers, 52.5 x 43.0 mm, 49 parts (0 on the bottom side), 30 nets.

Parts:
C1, C2, C4, C7, C9, C24: 0.1uF; C_1206_3216Metric_Pad1.33x1.80mm_HandSolder
C3, C5: 12pF; C_0402_1005Metric_Pad0.74x0.62mm_HandSolder
C22: 1uF; CP_Elec_4x5.4
C23, C26: 10uF; C_0805_2012Metric_Pad1.18x1.45mm_HandSolder
C25: 22uF; C_0805_2012Metric_Pad1.18x1.45mm_HandSolder
C27, C28, C29: 22uF; C_0603_1608Metric_Pad1.08x0.95mm_HandSolder
D1, D4, D5, D6: LED; LED_0402_1005Metric_Pad0.77x0.64mm_HandSolder
D3: SMAJ12A; D_SMA_Handsoldering
IC1: ESP32-WROOM-32D_M113DH2800PH3Q0; ESP32-WROOM-32D_ANT_SILK_REMOVED
J1: 2_54mm_PinHeader1x4; PinHeader_1x04_P2.54mm_Vertical
J3: Screw_Terminal_3.5mm_4; TerminalBlock_4Ucon_1x04_P3.50mm_Horizontal
J4: M50-3140645R; HARWIN_M50-3140645R
L2: 2uH; SRN8040-2R2Y
Q1, Q2: DSS4160U-7; SOT65P210X110-3N
R1: 120R; R_1206_3216Metric_Pad1.30x1.75mm_HandSolder
R2, R14: 620R; R_0805_2012Metric_Pad1.20x1.40mm_HandSolder
R3, R16, R17, R18: 2K; R_0603_1608Metric_Pad0.98x0.95mm_HandSolder
R4, R5, R13, R19, R20, R22: 10K; R_0805_2012Metric_Pad1.20x1.40mm_HandSolder
R15: 47K; R_0805_2012Metric_Pad1.20x1.40mm_HandSolder
R21: 33.2K; R_0805_2012Metric_Pad1.20x1.40mm_HandSolder
RX2_TP1: 5029; KEYSTONE_5029
SW3, SW4: 3983; SW_3983_ADA
TX2_TP2: 5029; KEYSTONE_5029
U3: MAX3485; SOIC-8_3.9x4.9mm_P1.27mm
U4: TPS563208DDCT; TPS563208DDCT_SOT95P280X110-6N
Y1: 32.768kHz; XTAL_ABS05-32.768KHZ-T

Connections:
/DTR: J4.4, Q1.2 (E), R20.1
/EN: C2.1, C4.1, IC1.3 (EN), Q2.3 (C), R4.2, SW4.2
/IO_0: C1.1, IC1.25 (IO0), Q1.3 (C), SW3.2
/LED_A: IC1.12 (IO27), R18.1
/LED_B: IC1.11 (IO26), R17.1
/LED_C: IC1.10 (IO25), R16.1
/RS485+: J3.2, R1.1, R2.1, U3.6 (A)
/RS485-: J3.3, R1.2, R14.2, U3.7 (B)
/RS485_DE_RE: IC1.23 (IO15), R15.2, U3.2 (~RE), U3.3 (DE)
/RTS: J4.5, Q2.2 (E), R19.1
/RX_0: IC1.34 (RXD0), J4.2
/RX_{2}: IC1.27 (IO16), RX2_TP1.TP, U3.1 (RO)
/SCL_BUS: IC1.36 (IO22), J1.2, R5.2
/SDA_BUS: IC1.33 (IO21), J1.3, R13.2
/TX_0: IC1.35 (TXD0), J4.3
/TX_{2}: IC1.28 (IO17), TX2_TP2.TP, U3.4 (DI)
/VBUS_12: C23.1, C26.2, D3.1 (A1), J3.1, U4.3 (VIN), U4.5 (EN)
/X32N: C3.2, IC1.9 (IO33), Y1.1
/X32P: C5.2, IC1.8 (IO32), Y1.2
GND: C1.2, C2.2, C3.1, C4.2, C5.1, C7.2, C22.2, C23.2, C24.1, C25.1, C26.1, C27.1, C28.1, C29.1, D1.1 (K), D3.2 (A2), D4.1 (K), D5.1 (K), D6.1 (K), IC1.1 (GND_1), IC1.15 (GND_2), IC1.38 (GND_3), IC1.39 (GND_4), J1.4, J3.4, J4.1, R14.1, R15.1, R22.1, SW3.1, SW4.1, U3.5 (GND), U4.1 (GND)
unnamed: D1.2 (A), R3.2
unnamed: D4.2 (A), R16.2
unnamed: D5.2 (A), R17.2
unnamed: D6.2 (A), R18.2
unnamed: Q1.1 (B), R19.2
unnamed: Q2.1 (B), R20.2
unnamed: C9.1, L2.2, U4.2 (SW)
unnamed: C9.2, U4.6 (VBST)
unnamed: R21.2, R22.2, U4.4 (VFB)
VDD33: C7.1, C22.1, C24.2, C25.2, C27.2, C28.2, C29.2, IC1.2 (3V3), J1.1, J4.6, L2.1, R2.2, R3.1, R4.1, R5.1, R13.1, R21.1, U3.8 (VCC)

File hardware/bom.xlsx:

Reference | Value | Datasheet | Footprint | Qty | PartNo | Description | In Inventory | Inventory Id
C1,C2,C4,C7,C9,C24 | 0.1uF | https://content.kemet.com/datasheets/KEM_C1002_X7R_SMD.pdf | Capacitor_SMD:C_1206_3216Metric_Pad1.33x1.80mm_HandSolder | 5 | C1206C104K5RACTU | 0.1 µF ±10% 50V Ceramic Capacitor X7R 1206 (3216 Metric) | TRUE | CAP#37
C3,C5 | 12pF | https://www.yageo.com/upload/media/product/productsearch/dat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 | Capacitor_SMD:C_0402_1005Metric_Pad0.74x0.62mm_HandSolder | 2 | CC0402FRNP09BN120 | 22 µF ±20% 6.3V Ceramic Capacitor X5R 0603 (1608 Metric) | TRUE | CAP#8
C22 | 1uF | https://www.niccomp.com/wp-content/uploads/catalog/nace.pdf | Capacitor_SMD:CP_Elec_4x5.4 | 1 | NACE1R0M50V4X5.5TR15F | 1 µF 50 V Aluminum Electrolytic Capacitors Radial, Can - SMD 19.9 Ohm 2000 Hrs 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 | TRUE | CAP#35
C23,C26 | 10uF | https://mm.digikey.com/Volume0/opasdata/d220001/medias/docus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 | Capacitor_SMD:C_0805_2012Metric_Pad1.18x1.45mm_HandSolder | 2 | MSAST219LB5106KTNA01 | 10 µF ±10% 25V Ceramic Capacitor X5R 0805 (2012 Metric) | FALSE
C25,C27,C28,C29 | 22uF | https://mm.digikey.com/Volume0/opasdata/d220001/medias/docus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 | Capacitor_SMD:C_0603_1608Metric_Pad1.08x0.95mm_HandSolder,Capacitor_SMD:C_0805_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 | 4 | CL21A226MOCLRNC | 22 µF ±20% 16V Ceramic Capacitor X5R 0805 (2012 Metric),22 µF ±20% 6.3V Ceramic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 | TRUE | CAP#17
D1,D4,D5,D6 | LED | https://www.mouser.dk/datasheet/2/588/asset_pdf_5057771-3418946.pdf | LED_SMD:LED_0402_1005Metric_Pad0.77x0.64mm_HandSolder | 4 | LW QH8G-Q2OO-3K5L-1 | LED White SMD | TRUE | OTHR#6
D3 | SMAJ12A | https://www.littelfuse.com/media?resourcetype=datasheets&ite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 | Diode_SMD:D_SMA_Handsoldering | 1 | SMAJ12A | 400W unidirectional Transient Voltage Suppressor, 12.0Vr, SMA(DO-214AC) | TRUE | D#5.1
IC1 | ESP32-WROOM-32D | https://www.espressif.com/sites/default/files/documentation/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 | project_footprints:ESP32-WROOM-32D_ANT_SILK_REMOVED | 1 | M113DH2800PH3Q0 | WiFi Modules (802.11) SMD Module, ESP32-D0WD, 32Mbits SPI flash, UART mode, PCB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 | TRUE | IC#38
J1 | 2_54mm_PinHeader1x4 |  | Connector_PinHeader_2.54mm:PinHeader_1x04_P2.54mm_Vertical | 1 | 2_54MM_PIN | Screw terminal | TRUE | N/A
J3 | Screw_Terminal_3.5mm_4 | https://cdn.sparkfun.com/assets/b/1/8/d/9/OSTTEXX0104.pdf | TerminalBlock_4Ucon:TerminalBlock_4Ucon_1x04_P3.50mm_Horizontal | 1 | Screw_Terminal_3.5mm_4 | Screw terminal | TRUE | N/A
L2 | 2uH | SRN8040-2R2Y | project_footprints:SRN8040-2R2Y | 1 | SRN8040-2R2Y | Inductor | FALSE
Q1,Q2 | DSS4160U-7 | https://www.diodes.com//assets/Datasheets/ds31684.pdf | project_footprints:SOT65P210X110-3N | 2 | DSS4160U-7 | Diodes Inc DSS4160U-7 NPN Bipolar Transistor, 1 A, 60 V, 3-Pin SOT-323 | TRUE | TRAN#7
R1 | 120R | https://www.yageo.com/upload/media/product/products/datashee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 | Resistor_SMD:R_1206_3216Metric_Pad1.30x1.75mm_HandSolder | 1 | RC1206FR-13120RL | 120 Ohms ±1% 0.25W, 1/4W Chip Resistor 1206 (3216 Metric) Moisture Resistant Th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 | TRUE | R#32
R2,R14 | 620R | https://media.distrelec.com/Web/Downloads/_t/ds/rnd_smd_resi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 | Resistor_SMD:R_0805_2012Metric_Pad1.20x1.40mm_HandSolder | 2 | RND 1550805S8F6200T5E | Resistor Thick film 620 Ohm ±1% SMD 0805 1/8W | TRUE | R#13
R3,R16,R17,R18 | 2K | https://media.distrelec.com/Web/Downloads/_t/ds/RND_155T_Thi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 | Resistor_SMD:R_0603_1608Metric_Pad0.98x0.95mm_HandSolder | 4 | RND 155TC0325B2001T5H | Resistor Thin film 2 KOhm ±0.1% SMD 0603 1/6W | TRUE | R#15
R4,R5,R13,R19,R20,R22 | 10K | https://media.distrelec.com/Web/Downloads/_t/ds/RND_155T_Thi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 | Resistor_SMD:R_0805_2012Metric_Pad1.20x1.40mm_HandSolder | 6 | RND 155TC0525B1002T5J | Resistor Thin film 10 KOhm ±0.1% SMD 0805 1/4W | FALSE
R15 | 47K | https://media.distrelec.com/Web/Downloads/_t/ds/rnd_smd_resi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 | Resistor_SMD:R_0805_2012Metric_Pad1.20x1.40mm_HandSolder | 1 | RND 1550805S8F4702T5E | Resistor Thick film 47 kOhm ±1% SMD 0805 1/8W | TRUE | R#24
R21 | 33.2K | https://www.vishay.com/docs/20035/dcrcwe3.pdf | Resistor_SMD:R_0805_2012Metric_Pad1.20x1.40mm_HandSolder | 1 | CRCW080533K2FKEA | 33.2 kOhms ±1% 0.125W, 1/8W Chip Resistor 0805 (2012 Metric) Automotive AEC-Q20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 | FALSE
RX2_TP1,TX2_TP2 | 5029 | https://www.keyelco.com/product-pdf.cfm?p=1358 | project_footprints:KEYSTONE_5029 | 2 | 5029 | PC Test Point, Miniature Phosphor Bronze Silver Plating Surface Mount Mounting 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 | FALSE
SW3,SW4 | 3983 | https://mm.digikey.com/Volume0/opasdata/d220001/medias/docus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 | project_footprints:SW_3983_ADA | 2 | Adafruit_3983 | Pushbutton Switch Standard Surface Mount | FALSE
U3 | MAX3485 | https://datasheets.maximintegrated.com/en/ds/MAX3483-MAX3491.pdf | Package_SO:SOIC-8_3.9x4.9mm_P1.27mm | 1 | MAX3485CSA+T | True RS-485/RS-422, 10Mbps, Slew-Rate Limited, with low-power shutdown, with re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 | TRUE | IC#36
Y1 | 32.768kHz | https://abracon.com/Resonators/ABS05.pdf | project_footprints:XTAL_ABS05-32.768KHZ-T | 1 | ABS05-32.768KHZ-T | 32.768 kHz ±20ppm Crystal 12.5pF 90 kOhms 2-SMD, No Lead | TRUE | OTHR#1
J4 | M50-3140645R |  | project_footprints:HARWIN_M50-3140645R | 1 | M50-3140645R |  | FALSE
U4 | TPS563208DDCT |  | project_footprints:TPS563208DDCT_SOT95P280X110-6N | 1 | TPS563208DDCT | Buck Switching Regulator IC Positive Adjustable 0.768V 1 Output 3A SOT-23-6 Thi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 | FALSE
